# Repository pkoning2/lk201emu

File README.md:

# Digital Equipment LK201 keyboard emulator

This project allows a standard USB PC keyboard to be used as replacement for a DEC LK201 keyboard.  It consists of a small circuit built around an Adafruit Trinket M0 Arduino processor, and software for that to implement a USB host driver for the USB keyboard and the LK201 communication protocol. 

Subdirectory `lk201` is the Arduino software.  You can build it using the standard Arduino SDK, or use the prebuilt binary.

Subdirectory `kicad` is the circuit board design.  You can view it using the open source KiCAD package.

Subdirectory `doc` contains several documentation files in MD format.  File `emulator.md` describes the features of the emulator; `kicad` describes the board design and assembly information, and `software` describes the software and the load procedure.  There are also two JPG files that show the circuit board.

File `LICENSE` is the open source license under which this emulator is released.

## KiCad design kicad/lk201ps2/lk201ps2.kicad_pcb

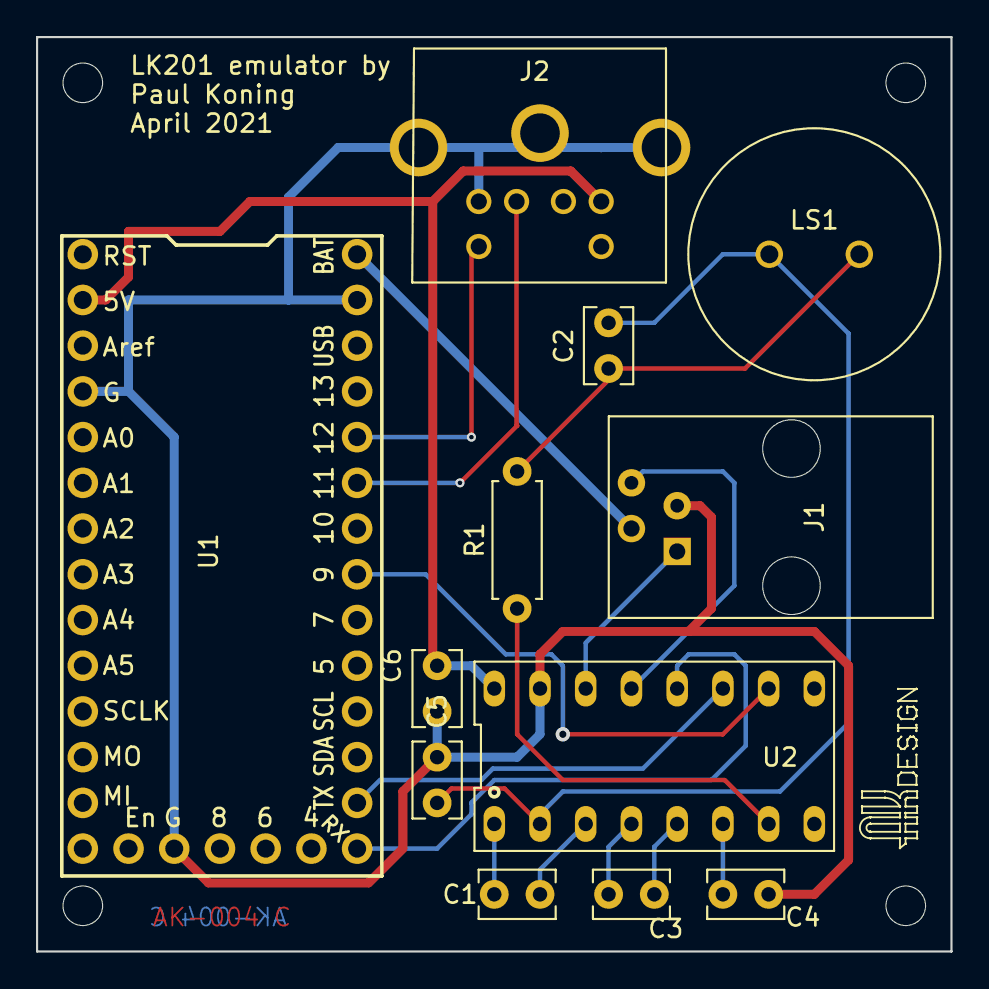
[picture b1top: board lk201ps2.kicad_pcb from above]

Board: 2 copper layers, 50.8 x 50.8 mm, 12 parts (0 on the bottom side), 18 nets.

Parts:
C1, C3, C4, C5, C6: 0.1uF; C_Rect_L4.0mm_W2.5mm_P2.54mm
C2: 0.01uF; C_Rect_L4.0mm_W2.5mm_P2.54mm
J1: RJ22
J2: Mini-DIN-6; MDJ-006
LS1: PS1420; PS1420_buzzer
R1: 3.3k; R_Axial_DIN0207_L6.3mm_D2.5mm_P7.62mm_Horizontal
U1: Itsy_Bitsy_5V; Itsy
U2: ICL3232CPZ; DIP-16_296_ELL

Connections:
/V5: C6.1, J2.4, U1.2, U2.16
/V12: J1.2, U1.33
/VS+: C2.2, C5.2, LS1.2, U2.2
GND: C4.1, C5.1, C6.2, J1.3, J2.3, J2.SH, U1.4, U1.16, U1.32, U2.15
unnamed: C1.1, U2.1
unnamed: C1.2, U2.3
unnamed: C2.1, LS1.1, R1.2
unnamed: C3.1, U2.4
unnamed: C3.2, U2.5
unnamed: C4.2, U2.6
unnamed: J1.1, U2.14
unnamed: J1.4, U2.13
unnamed: J2.1, U1.28
unnamed: J2.5, U1.29
unnamed: R1.1, U2.7
unnamed: U1.20, U2.12
unnamed: U1.21, U2.11
unnamed: U1.26, U2.10

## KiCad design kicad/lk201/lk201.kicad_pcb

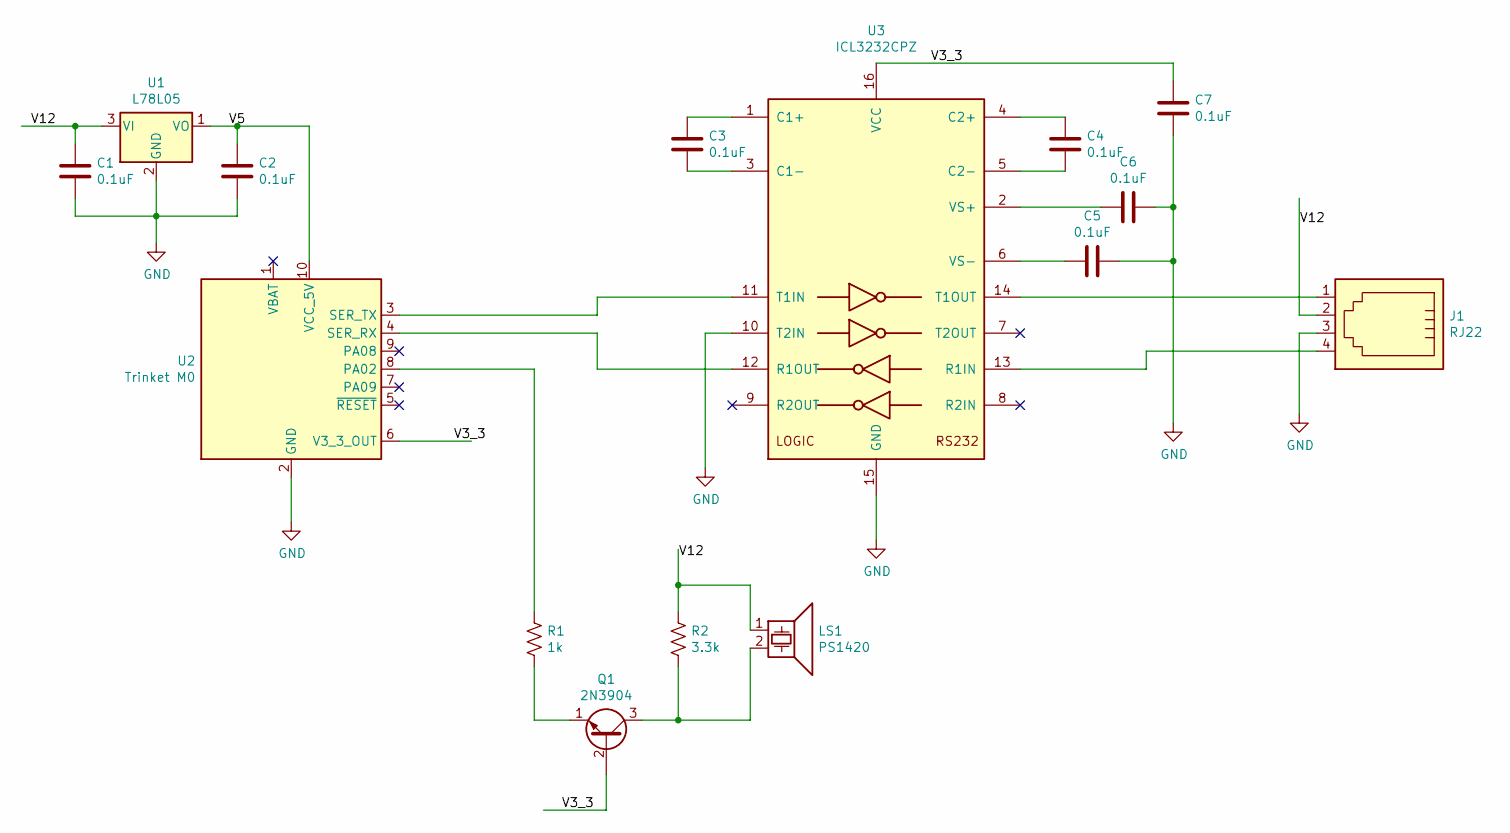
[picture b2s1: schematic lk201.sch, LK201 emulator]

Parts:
C1, C2, C3, C4, C5, C6, C7: 0.1uF; C_Rect_L4.0mm_W2.5mm_P2.54mm
J1: RJ22; Mfg part A-2004-3-4-LP-N-R; Digikey ​AE10381-ND
LS1: PS1420; PS1420_buzzer
Q1: 2N3904; TO-92_Inline_Narrow_Oval
R1: 1k; R_Axial_DIN0207_L6.3mm_D2.5mm_P7.62mm_Horizontal; Mfg part CF14JT1K00; Digikey CF14JT1K00CT-ND
R2: 3.3k; R_Axial_DIN0207_L6.3mm_D2.5mm_P7.62mm_Horizontal; Mfg part CF14JT3K30; Digikey CF14JT3K30TR-ND
U1: L78L05; TO-92_Inline_Narrow_Oval
U2: Trinket M0; Trinket_M0; Mfg part 3500; Digikey 1528-2361-ND
U3: ICL3232CPZ; DIP-16_296_ELL; Mfg part ICL3232CPZ; Digikey ICL3232CPZ-ND​

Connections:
/V3_3: C7.1, Q1.2 (B), U2.6 (V3_3_OUT), U3.16 (VCC)
/V5: C2.1, U1.1 (VO), U2.10 (VCC_5V)
/V12: C1.1, J1.2, LS1.1, R2.1, U1.3 (VI)
GND: C1.2, C2.2, C5.1, C6.1, C7.2, J1.3, U1.2 (GND), U2.2 (GND), U3.10 (T2IN), U3.15 (GND)
unnamed: C3.1, U3.1 (C1+)
unnamed: C3.2, U3.3 (C1-)
unnamed: C4.1, U3.4 (C2+)
unnamed: C4.2, U3.5 (C2-)
unnamed: C5.2, U3.6 (VS-)
unnamed: C6.2, U3.2 (VS+)
unnamed: J1.1, U3.14 (T1OUT)
unnamed: J1.4, U3.13 (R1IN)
unnamed: LS1.2, Q1.3 (C), R2.2
unnamed: Q1.1 (E), R1.2
unnamed: R1.1, U2.8 (PA02)
unnamed: U2.3 (SER_TX), U3.11 (T1IN)
unnamed: U2.4 (SER_RX), U3.12 (R1OUT)

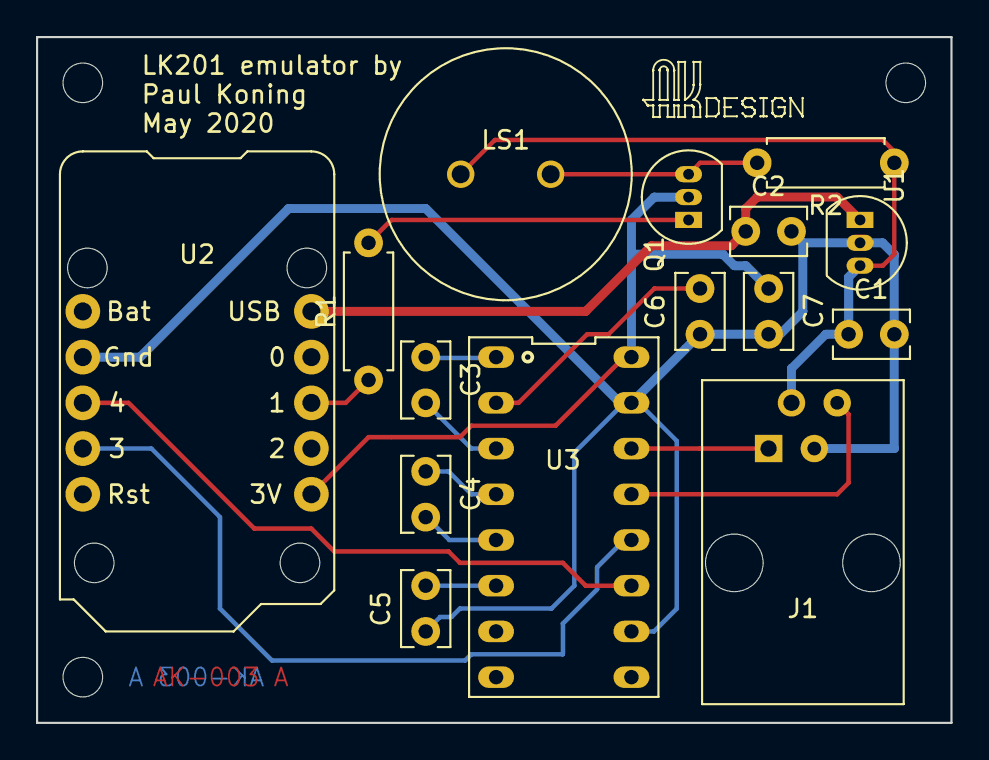
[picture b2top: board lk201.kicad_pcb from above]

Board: 2 copper layers, 50.8 x 38.1 mm, 15 parts (0 on the bottom side), 17 nets.

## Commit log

2020-06-20 Initial delivery.
2020-06-20 Fix file mixup
2020-08-19 Add pointer to Digikey saved BOM.
2020-12-25 Fix wrong code for F9. Binary (lk201.uf2) updated to match.
2021-03-07 Initial commit of PS-2 version of keybaord emulator.
2021-04-03 1. Update board date. This is board rev C 2. Bugfixes in scan software, fix a race condition between timing out keyboard data start and the arrival of the start bit. This requires holding clock low l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
2021-04-17 Remove line missed in previous cleanup.
2021-04-17 Update board doc to point to OSHPark shared design file for PS2 board.
2021-05-11 Add public BOM link for PS2 based LK201 emulator.
2021-05-18 Tweak .gitignore
2021-05-26 Fix build instructions, reported by Toncho11
2021-05-26 Mention that the RJ22 has to be unplugged for USB emulator programming as well.
2021-05-26 Correction
2021-05-26 red diode clarification
2021-08-11 Document alternate parts, thanks to Toncho11.
